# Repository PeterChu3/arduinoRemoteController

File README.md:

# arduinoRemoteController
A PCB with ATmega328p on board to control other ATmega328p remotely

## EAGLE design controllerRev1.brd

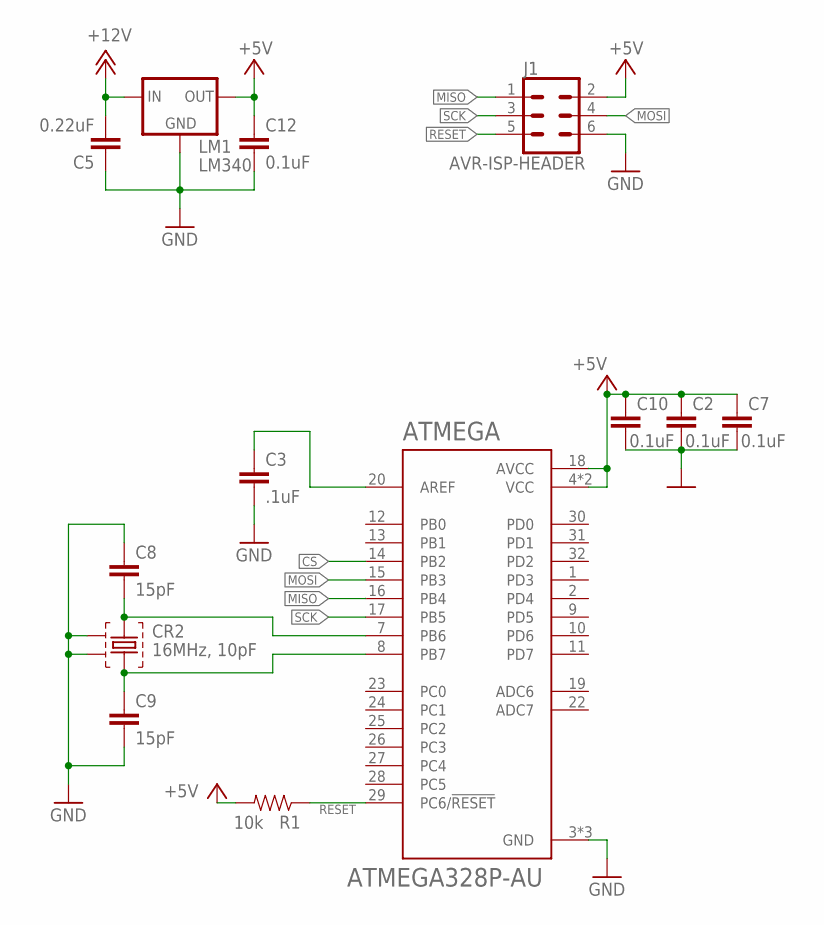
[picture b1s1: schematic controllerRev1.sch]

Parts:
ATMEGA: ATMEGA328P-AU; QFP80P900X900X120-32N
C2, C7, C10, C12: 0.1uF; 0603-CAP
C3: .1uF; 0603-CAP
C5: 0.22uF; 0603-CAP
C8, C9: 15pF; 0603-CAP
CR2: 16MHz, 10pF; ABM3B
J1: AVR-ISP-HEADER; 2X03
LM1: LM340; SOT223
R1: 10k; 0603-RES

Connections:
+5V: ATMEGA.4 (VCC), ATMEGA.6 (VCC), ATMEGA.18 (AVCC), C2.1, C7.1, C10.1, C12.1, J1.2, LM1.3 (OUT), R1.2
+12V: C5.2, LM1.1 (IN)
CS: ATMEGA.14 (PB2)
GND: ATMEGA.3 (GND), ATMEGA.5 (GND), ATMEGA.21 (GND), C2.2, C3.2, C5.1, C7.2, C8.1, C9.2, C10.2, C12.2, CR2.GND, CR2.GND2, J1.6, LM1.2 (GND), LM1.4 (GND)
MISO: ATMEGA.16 (PB4), J1.1
MOSI: ATMEGA.15 (PB3), J1.4
unnamed: ATMEGA.7 (PB6), C8.2, CR2.1
unnamed: ATMEGA.8 (PB7), C9.1, CR2.3
unnamed: ATMEGA.20 (AREF), C3.1
RESET: ATMEGA.29 (PC6/!RESET), J1.5, R1.1
SCK: ATMEGA.17 (PB5), J1.3

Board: 2 copper layers, 13 parts (0 on the bottom side), 10 nets, no tracks yet.

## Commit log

2021-01-16 Added board and schematic
